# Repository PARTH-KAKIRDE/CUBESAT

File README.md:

# EPS — Electrical Power System

Power management module for the 2U CubeSat.

## Overview
Handles solar power generation, battery charging, and regulated power distribution to all subsystems (OBC, COMMS, ADCS, Payload).

## Contents
- `CubeSat_EPS/` — KiCad project (schematic + PCB + fabrication PDF)
  - `CubeSat_EPS.kicad_sch` — Schematic
  - `CubeSat_EPS.kicad_pcb` — PCB layout
  - `CubeSat_EPS.kicad_pro` — Project configuration
  - `CubeSat_EPS.pdf` — Schematic PDF export

## Tool
Designed in KiCad 7/8. Open `CubeSat_EPS.kicad_pro` to view the full project.

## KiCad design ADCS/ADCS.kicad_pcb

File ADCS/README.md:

# ADCS — Attitude Determination and Control System

STM32F446 board that reads the six sun sensors and drives the three magnetorquers (DRV8833 X/Y/Z).

## Contents
- `ADCS.kicad_sch` — Schematic
- `ADCS.kicad_pcb` — PCB layout (84 × 84 mm, 2 layers)
- `ADCS.kicad_pro` — Project configuration
- `fp-lib-table`, `Library.pretty/` — project footprint library (Tag-Connect TC2030 SWD)

## Protection and reliability changes
- Input protection on 5V and 3.3V: PTC fuses (F1 0.75 A, F2 0.5 A), reverse-polarity P-MOSFETs (Q1/Q2 AO3401A), TVS diodes (D1 SMBJ5.0A, D2 SMBJ3.3A)
- ESD diodes (ESD5B5) on the six sun-sensor inputs and both I2C buses (D3–D12)
- Decoupling: 47 µF bulk on 5V, 10 µF + 4.7 µF + 100 nF on 3.3V
- DRV8833 nFAULT lines pulled **up** to 3.3V (R12–R14, 10k); the pin is open-drain
- Current-sense outputs filtered (1k + 100 nF) before the ADC
- I2C pull-ups (4.7k), BOOT0 pull-down (10k)
- Single GND–GNDA tie (R20, 0R)
- Four 4 mm mounting holes, 75 mm spacing

## Checks
KiCad 10.0.6: DRC 0 violations, 0 unconnected pads. Two warnings: the F1/F2 footprints do not match the symbol's footprint filter (footprint is correct).

## Tool
Designed in KiCad 10. Open `ADCS.kicad_pro` to view the full project.

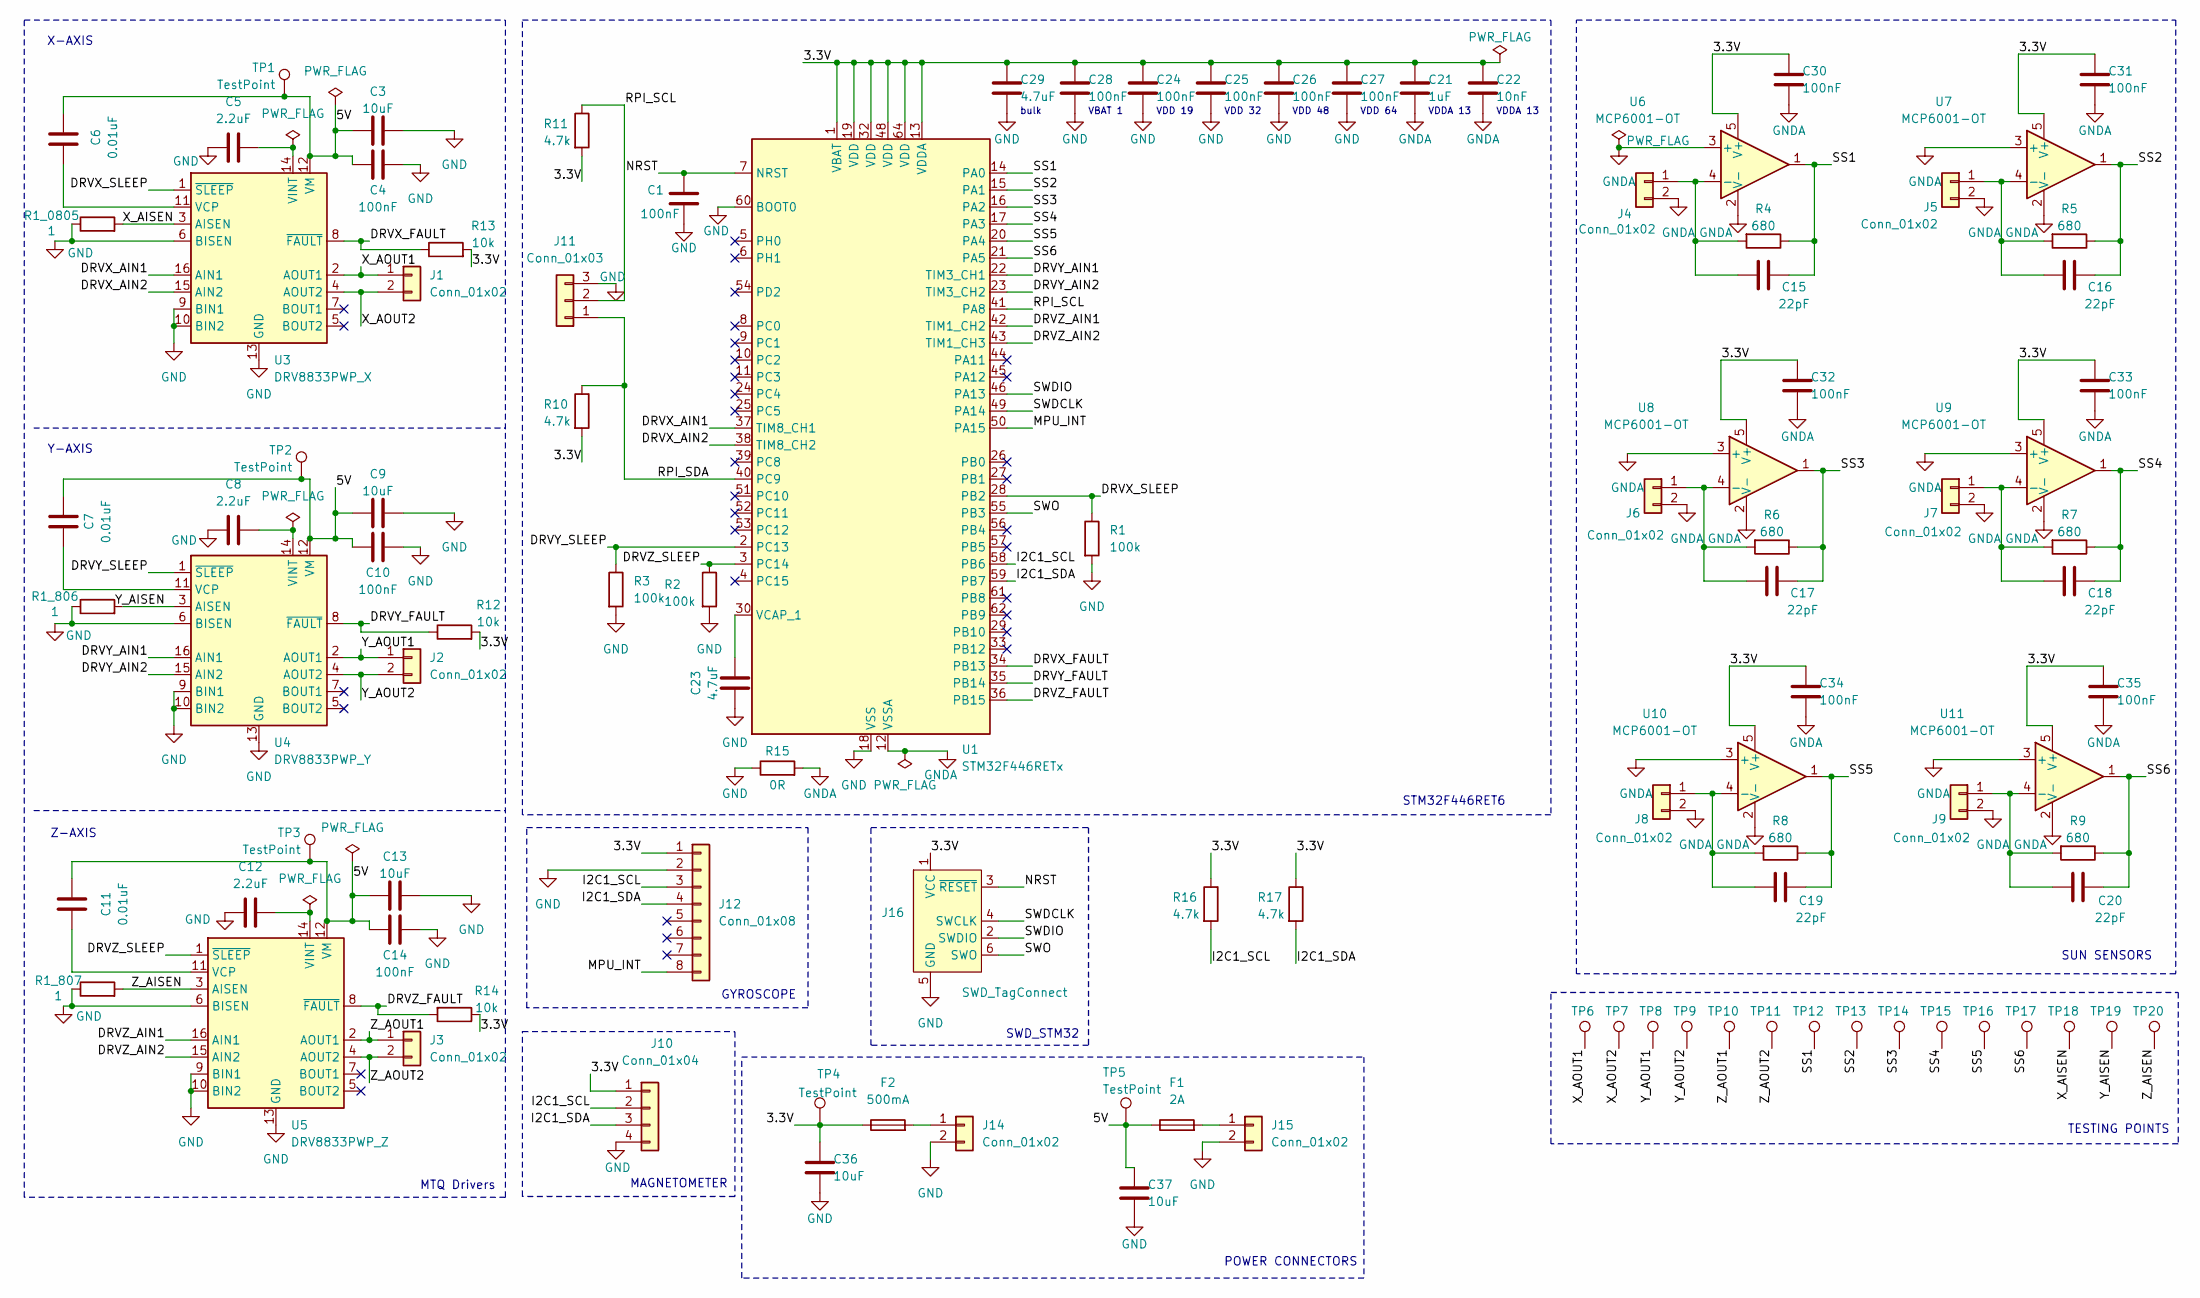
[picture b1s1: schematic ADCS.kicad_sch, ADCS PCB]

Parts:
C1, C4, C10, C14: 100nF; C_0805_2012Metric_Pad1.18x1.45mm_HandSolder
C3, C9, C13: 10uF; C_0805_2012Metric_Pad1.18x1.45mm_HandSolder
C5, C8, C12: 2.2uF; C_0805_2012Metric_Pad1.18x1.45mm_HandSolder
C6, C7, C11: 0.01uF; C_0805_2012Metric_Pad1.18x1.45mm_HandSolder
C15, C16, C17, C18, C19, C20: 22pF; C_0805_2012Metric_Pad1.18x1.45mm_HandSolder
C21: 1uF; C_0805_2012Metric_Pad1.18x1.45mm_HandSolder
C22: 10nF; C_0805_2012Metric_Pad1.18x1.45mm_HandSolder
C23, C29: 4.7uF; C_0805_2012Metric_Pad1.18x1.45mm_HandSolder
C24, C25, C26, C27, C28, C30, C31, C32, C33, C34, C35: 100nF; C_0603_1608Metric_Pad1.08x0.95mm_HandSolder
C36, C37: 10uF; C_1206_3216Metric_Pad1.33x1.80mm_HandSolder
F1: 2A; Fuse_1206_3216Metric_Pad1.42x1.75mm_HandSolder
F2: 500mA; Fuse_1206_3216Metric_Pad1.42x1.75mm_HandSolder
J1, J2, J3, J4, J5, J6, J7, J8, J9: Conn_01x02; JST_PH_B2B-PH-K_1x02_P2.00mm_Vertical
J10: Conn_01x04; JST_PH_B4B-PH-K_1x04_P2.00mm_Vertical
J11: Conn_01x03; JST_PH_B3B-PH-K_1x03_P2.00mm_Vertical
J12: Conn_01x08; JST_PH_B8B-PH-K_1x08_P2.00mm_Vertical
J14, J15: Conn_01x02; JST_XH_B2B-XH-AM_1x02_P2.50mm_Vertical
J16: SWD_TagConnect; Tag-Connect_TC2030-IDC-NL_2x03_P1.27mm_Vertical
R1, R2, R3: 100k; R_0805_2012Metric_Pad1.20x1.40mm_HandSolder
R1_0805, R1_806, R1_807: 1; R_0805_2012Metric_Pad1.20x1.40mm_HandSolder
R4, R5, R6, R7, R8, R9: 680; R_0805_2012Metric_Pad1.20x1.40mm_HandSolder
R10, R11, R16, R17: 4.7k; R_0805_2012Metric_Pad1.20x1.40mm_HandSolder
R12, R13, R14: 10k; R_0805_2012Metric_Pad1.20x1.40mm_HandSolder
R15: 0R; R_0805_2012Metric_Pad1.20x1.40mm_HandSolder
TP1, TP2, TP3, TP4, TP5, TP6, TP7, TP8, TP9, TP10, TP11, TP12, TP13, TP14, TP15, TP16, TP17, TP18, TP19, TP20: TestPoint; TestPoint_Pad_1.0x1.0mm
U1: STM32F446RETx; LQFP-64_10x10mm_P0.5mm
U3: DRV8833PWP_X; HTSSOP-16-1EP_4.4x5mm_P0.65mm_EP3.4x5mm_Mask2.46x2.31mm_The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
U4: DRV8833PWP_Y; HTSSOP-16-1EP_4.4x5mm_P0.65mm_EP3.4x5mm_Mask2.46x2.31mm_The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
U5: DRV8833PWP_Z; HTSSOP-16-1EP_4.4x5mm_P0.65mm_EP3.4x5mm_Mask2.46x2.31mm_The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
U6, U7, U8, U9, U10, U11: MCP6001-OT; SOT-23-5

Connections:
/3.3V: C21.1, C22.1, C24.1, C25.1, C26.1, C27.1, C28.1, C29.1, C30.1, C31.1, C32.1, C33.1, C34.1, C35.1, C36.1, F2.1, J10.1, J12.1, J16.1 (VCC), R10.2, R11.2, R12.2, R13.2, R14.1, R16.1, R17.1, TP4.1 (1_1), U1.1 (VBAT), U1.13 (VDDA), U1.19 (VDD), U1.32 (VDD), U1.48 (VDD), U1.64 (VDD), U6.5 (V+), U7.5 (V+), U8.5 (V+), U9.5 (V+), U10.5 (V+), U11.5 (V+)
/5V: C3.1, C4.1, C6.2, C7.2, C9.1, C10.1, C11.2, C13.1, C14.1, C37.1, F1.1, TP1.1 (1_1), TP2.1 (1_1), TP3.1 (1_1), TP5.1 (1_1), U3.12 (VM), U4.12 (VM), U5.12 (VM)
/DRVX_AIN1: U1.37 (TIM8_CH1), U3.16 (AIN1)
/DRVX_AIN2: U1.38 (TIM8_CH2), U3.15 (AIN2)
/DRVX_FAULT: R13.1, U1.34 (PB13), U3.8 (~FAULT)
/DRVX_SLEEP: R1.1, U1.28 (PB2), U3.1 (~SLEEP)
/DRVY_AIN1: U1.22 (TIM3_CH1), U4.16 (AIN1)
/DRVY_AIN2: U1.23 (TIM3_CH2), U4.15 (AIN2)
/DRVY_FAULT: R12.1, U1.35 (PB14), U4.8 (~FAULT)
/DRVY_SLEEP: R3.1, U1.2 (PC13), U4.1 (~SLEEP)
/DRVZ_AIN1: U1.42 (TIM1_CH2), U5.16 (AIN1)
/DRVZ_AIN2: U1.43 (TIM1_CH3), U5.15 (AIN2)
/DRVZ_FAULT: R14.2, U1.36 (PB15), U5.8 (~FAULT)
/DRVZ_SLEEP: R2.1, U1.3 (PC14), U5.1 (~SLEEP)
/I2C1_SCL: J10.2, J12.3, R16.2, U1.58 (PB6)
/I2C1_SDA: J10.3, J12.4, R17.2, U1.59 (PB7)
/MPU_INT: J12.8, U1.50 (PA15)
/NRST: C1.1, J16.3 (~RESET), U1.7 (NRST)
/RPI_SCL: J11.2, R11.1, U1.41 (PA8)
/RPI_SDA: J11.1, R10.1, U1.40 (PC9)
/SS1: C15.1, R4.1, TP12.1 (1_1), U1.14 (PA0), U6.1
/SS2: C16.1, R5.1, TP13.1 (1_1), U1.15 (PA1), U7.1
/SS3: C17.1, R6.1, TP14.1 (1_1), U1.16 (PA2), U8.1
/SS4: C18.1, R7.1, TP15.1 (1_1), U1.17 (PA3), U9.1
/SS5: C19.1, R8.1, TP16.1 (1_1), U1.20 (PA4), U10.1
/SS6: C20.1, R9.1, TP17.1 (1_1), U1.21 (PA5), U11.1
/SWDCLK: J16.4 (SWCLK), U1.49 (PA14)
/SWDIO: J16.2 (SWDIO), U1.46 (PA13)
/SWO: J16.6 (SWO), U1.55 (PB3)
/X_AISEN: R1_0805.2, TP18.1 (1_1), U3.3 (AISEN)
/X_AOUT1: J1.1, TP6.1 (1_1), U3.2 (AOUT1)
/X_AOUT2: J1.2, TP7.1 (1_1), U3.4 (AOUT2)
/Y_AISEN: R1_806.2, TP19.1 (1_1), U4.3 (AISEN)
/Y_AOUT1: J2.1, TP8.1 (1_1), U4.2 (AOUT1)
/Y_AOUT2: J2.2, TP9.1 (1_1), U4.4 (AOUT2)
/Z_AISEN: R1_807.2, TP20.1 (1_1), U5.3 (AISEN)
/Z_AOUT1: J3.1, TP10.1 (1_1), U5.2 (AOUT1)
/Z_AOUT2: J3.2, TP11.1 (1_1), U5.4 (AOUT2)
GND: C1.2, C3.2, C4.2, C5.1, C8.1, C9.2, C10.2, C12.1, C13.2, C14.2, C23.1, C24.2, C25.2, C26.2, C27.2, C28.2, C29.2, C36.2, C37.2, J10.4, J11.3, J12.2, J14.2, J15.2, J16.5 (GND), R1.2, R1_0805.1, R1_806.1, R1_807.1, R2.2, R3.2, R15.1, U1.18 (VSS), U1.31 (VSS), U1.47 (VSS), U1.60 (BOOT0), U1.63 (VSS), U3.6 (BISEN), U3.9 (BIN1), U3.10 (BIN2), U3.13 (GND), U3.17 (GND), U4.6 (BISEN), U4.9 (BIN1), U4.10 (BIN2), U4.13 (GND), U4.17 (GND), U5.6 (BISEN), U5.9 (BIN1), U5.10 (BIN2), U5.13 (GND), U5.17 (GND)
GNDA: C21.2, C22.2, C30.2, C31.2, C32.2, C33.2, C34.2, C35.2, J4.2, J5.2, J6.2, J7.2, J8.2, J9.2, R15.2, U1.12 (VSSA), U6.2 (V-), U6.3 (+), U7.2 (V-), U7.3 (+), U8.2 (V-), U8.3 (+), U9.2 (V-), U9.3 (+), U10.2 (V-), U10.3 (+), U11.2 (V-), U11.3 (+)
unnamed: C15.2, J4.1, R4.2, U6.4 (-)
unnamed: C16.2, J5.1, R5.2, U7.4 (-)
unnamed: C17.2, J6.1, R6.2, U8.4 (-)
unnamed: C18.2, J7.1, R7.2, U9.4 (-)
unnamed: C19.2, J8.1, R8.2, U10.4 (-)
unnamed: C20.2, J9.1, R9.2, U11.4 (-)
unnamed: F2.2, J14.1
unnamed: F1.2, J15.1
unnamed: C23.2, U1.30 (VCAP_1)
unnamed: C6.1, U3.11 (VCP)
unnamed: C5.2, U3.14 (VINT)
unnamed: C7.1, U4.11 (VCP)
unnamed: C8.2, U4.14 (VINT)
unnamed: C11.1, U5.11 (VCP)
unnamed: C12.2, U5.14 (VINT)

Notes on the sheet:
VDD 19
MTQ Drivers
VDDA 13
TESTING POINTS
bulk
GYROSCOPE
MAGNETOMETER
VBAT 1
Z-AXIS
VDD 64
SUN SENSORS
VDD 32
POWER CONNECTORS
Y-AXIS
VDD 48
STM32F446RET6
SWD_STM32
X-AXIS

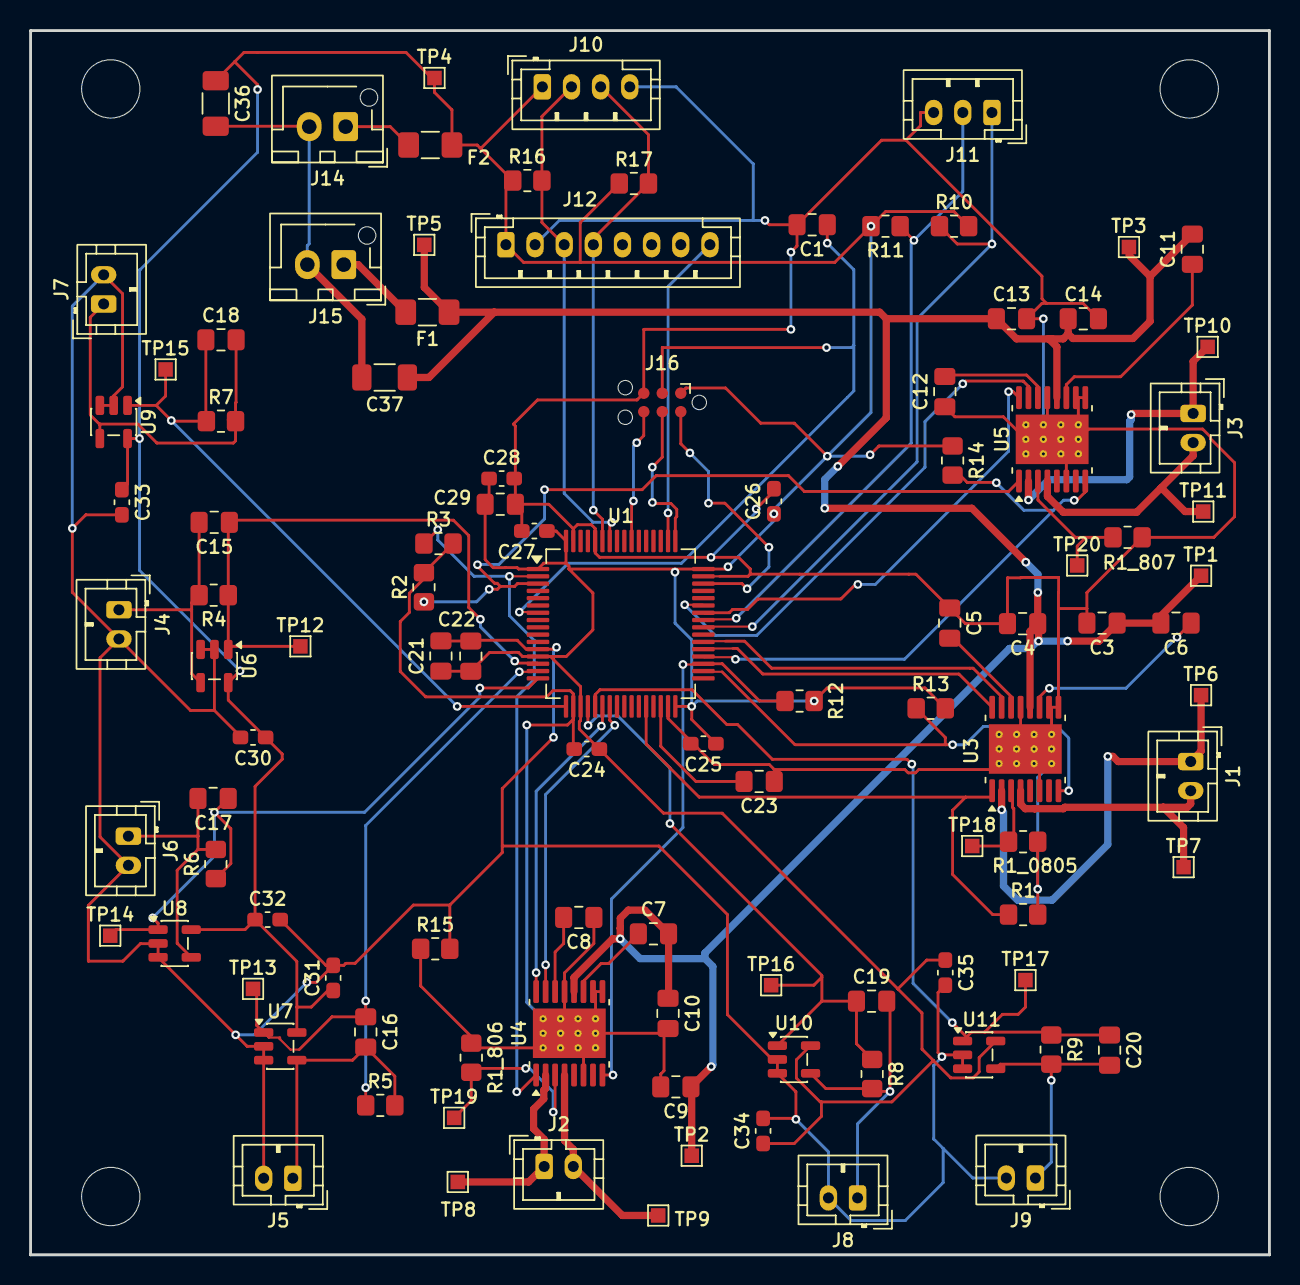
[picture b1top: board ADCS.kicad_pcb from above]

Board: 2 copper layers, 85.0 x 84.0 mm, 107 parts (0 on the bottom side), 55 nets.

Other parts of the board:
H1, H2, H3, H4: MountingHole_4mm

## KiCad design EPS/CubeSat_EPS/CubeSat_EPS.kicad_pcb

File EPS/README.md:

# EPS — Electrical Power System

Power management module for the 2U CubeSat.

## Overview
Handles solar power generation, battery charging, and regulated power distribution to all subsystems (OBC, COMMS, ADCS, Payload).

## Contents
- `CubeSat_EPS/` — KiCad project (schematic + PCB + fabrication PDF)
  - `CubeSat_EPS.kicad_sch` — Schematic
  - `CubeSat_EPS.kicad_pcb` — PCB layout
  - `CubeSat_EPS.kicad_pro` — Project configuration
  - `CubeSat_EPS.pdf` — Schematic PDF export

## Tool
Designed in KiCad 7/8. Open `CubeSat_EPS.kicad_pro` to view the full project.

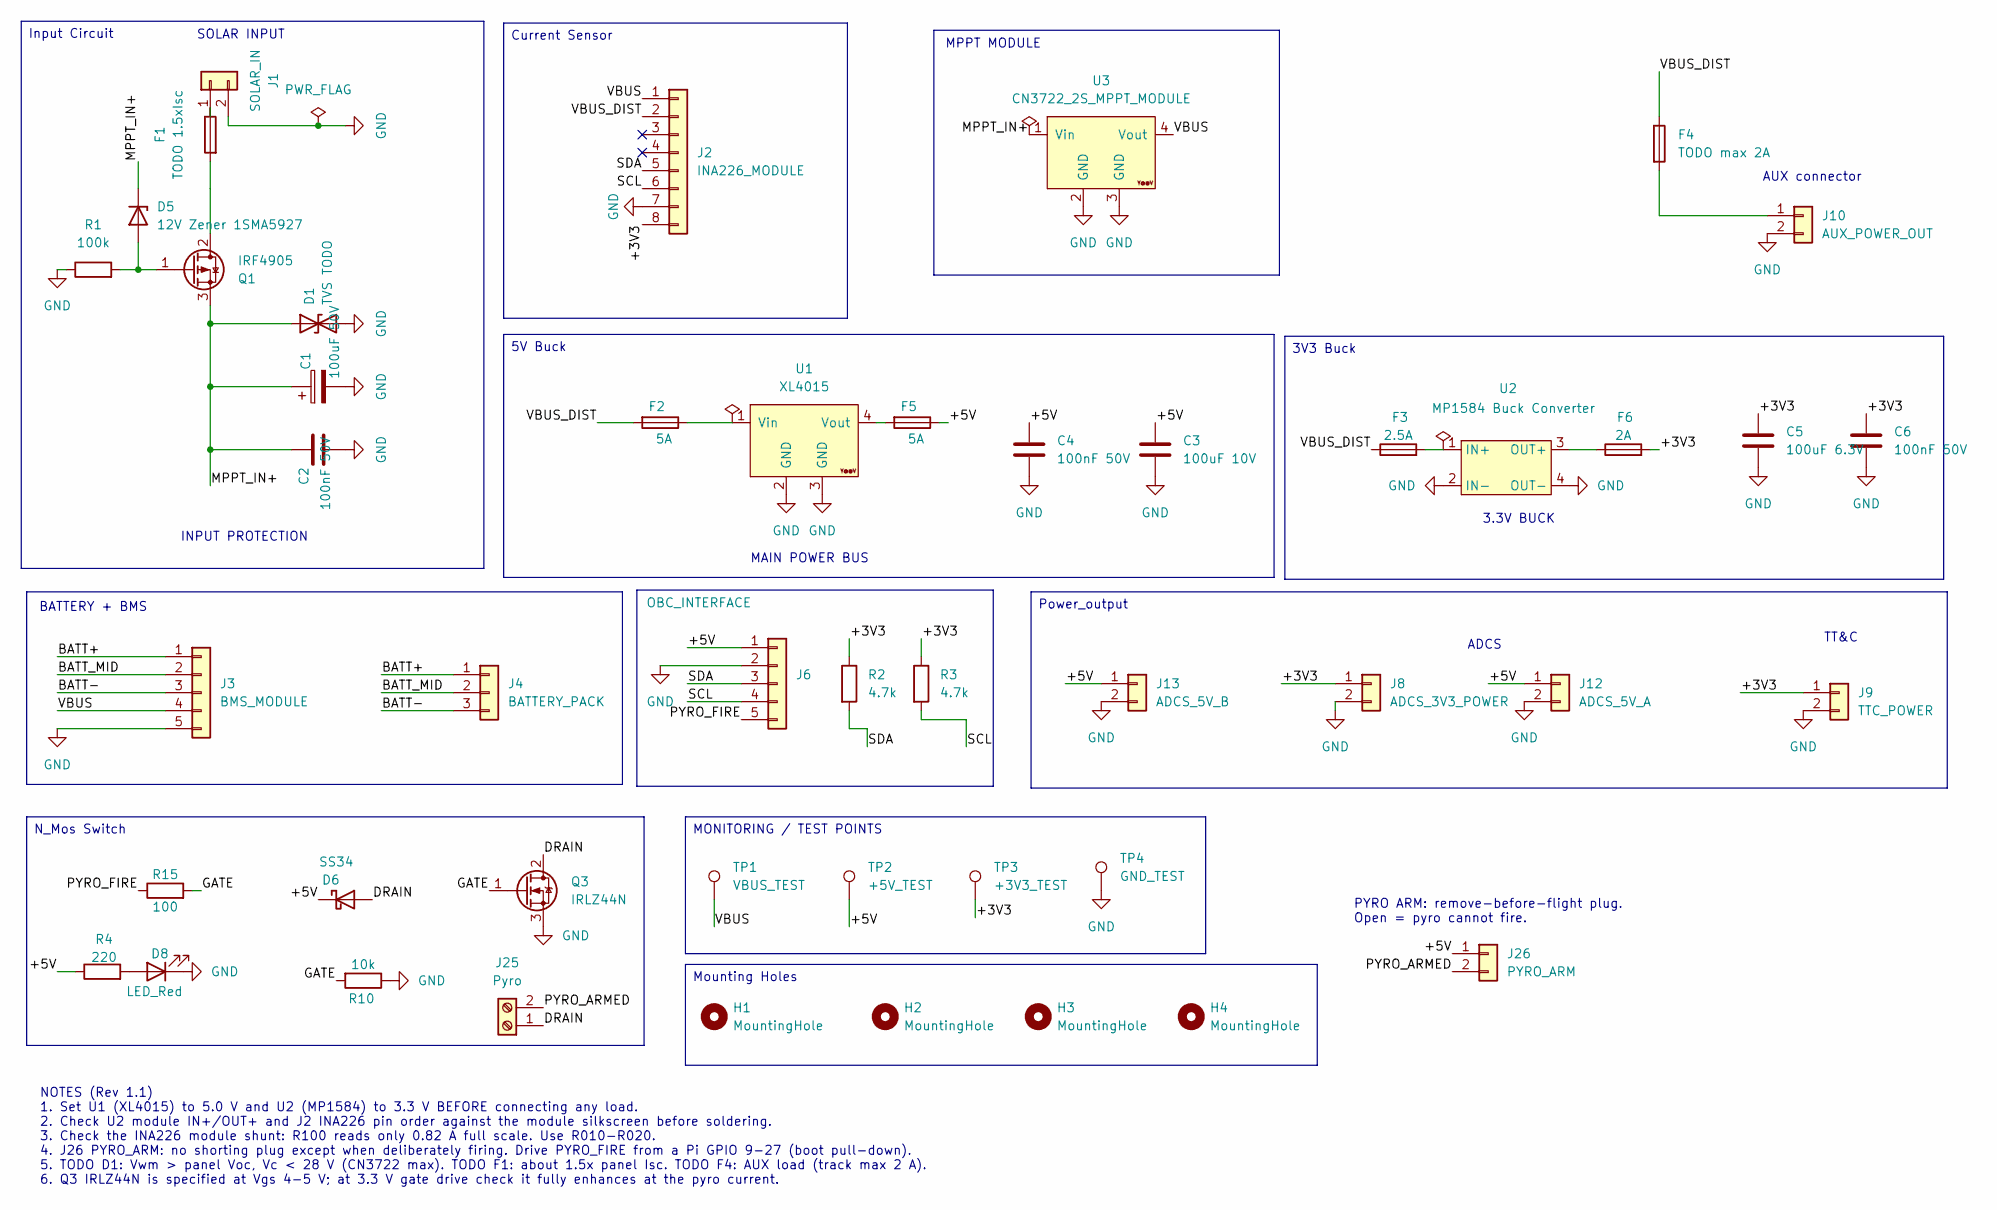
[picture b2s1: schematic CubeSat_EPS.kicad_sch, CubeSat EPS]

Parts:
C1: 100uF 50V; CP_Elec_6.3x7.7
C2, C4, C6: 100nF 50V; C_0805_2012Metric
C3: 100uF 10V; C_1206_3216Metric_Pad1.33x1.80mm_HandSolder
C5: 100uF 6.3V; C_0805_2012Metric_Pad1.18x1.45mm_HandSolder
D1: TVS TODO; D_SOD-123
D5: 12V Zener 1SMA5927; D_SMA
D6: SS34; D_SMA
D8: LED_Red; LED_0805_2012Metric_Pad1.15x1.40mm_HandSolder
F1: TODO 1.5xIsc; Fuse_1206_3216Metric
F2, F5: 5A; Fuse_1206_3216Metric
F3: 2.5A; Fuse_1206_3216Metric
F4: TODO max 2A; Fuse_1206_3216Metric
F6: 2A; Fuse_1206_3216Metric
H1, H2, H3, H4: MountingHole; MountingHole_4.3mm_M4
J1: SOLAR_IN; JST_VH_B2P-VH_1x02_P3.96mm_Vertical
J2: INA226_MODULE; INA226 Current Sensor
J3: BMS_MODULE; JST_VH_B5P-VH-B_1x05_P3.96mm_Vertical
J4: BATTERY_PACK; JST_VH_B3P-VH-B_1x03_P3.96mm_Vertical
J6: OBC_INTERFACE; JST_VH_B5P-VH_1x05_P3.96mm_Vertical
J8: ADCS_3V3_POWER; JST_VH_B2P-VH_1x02_P3.96mm_Vertical
J9: TTC_POWER; JST_VH_B2P-VH_1x02_P3.96mm_Vertical
J10: AUX_POWER_OUT; JST_VH_B2P-VH_1x02_P3.96mm_Vertical
J12: ADCS_5V_A; JST_VH_B2P-VH-B_1x02_P3.96mm_Vertical
J13: ADCS_5V_B; JST_VH_B2P-VH-B_1x02_P3.96mm_Vertical
J25: Pyro; TerminalBlock_TE_282834-2_1x02_P2.54mm_Horizontal
J26: PYRO_ARM; JST_VH_B2P-VH_1x02_P3.96mm_Vertical
Q1: IRF4905; TO-220-3_Vertical
Q3: IRLZ44N; TO-220-3_Vertical
R1: 100k; R_0805_2012Metric
R2, R3: 4.7k; R_0805_2012Metric
R4: 220; R_0805_2012Metric_Pad1.20x1.40mm_HandSolder
R10: 10k; R_0805_2012Metric_Pad1.20x1.40mm_HandSolder
R15: 100; R_0805_2012Metric_Pad1.20x1.40mm_HandSolder
TP1: VBUS_TEST; TestPoint_Pad_D1.5mm
TP2: +5V_TEST; TestPoint_Plated_Hole_D2.0mm
TP3: +3V3_TEST; TestPoint_Plated_Hole_D2.0mm
TP4: GND_TEST; TestPoint_Plated_Hole_D2.0mm
U1: XL4015; XL4015 Buck
U2: MP1584 Buck Converter; MP1584 module 20mm_15mm
U3: CN3722_2S_MPPT_MODULE; MPPT Solar

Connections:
/+3V3: C5.1, C6.1, F6.2, J2.8, J8.1, J9.1, R2.1, R3.1, TP3.1 (1_1)
/+5V: C3.1, C4.1, D6.1 (K), F5.1, J6.1, J12.1, J13.1, J26.1, R4.1, TP2.1 (1_1)
/BATT+: J3.1, J4.1
/BATT-: J3.3, J4.3
/BATT_MID: J3.2, J4.2
/DRAIN: D6.2 (A), J25.1, Q3.2 (D)
/GATE: Q3.1 (G), R10.2, R15.2
/MPPT_IN+: C1.1, C2.1, D1.1 (A1), D5.1 (K), Q1.3 (S), U3.1 (Vin)
/PYRO_ARMED: J25.2, J26.2
/PYRO_FIRE: J6.5, R15.1
/SCL: J2.6, J6.4, R3.2
/SDA: J2.5, J6.3, R2.2
/VBUS: J2.1, J3.4, TP1.1 (1_1), U3.4 (Vout)
/VBUS_DIST: F2.2, F3.1, F4.1, J2.2
GND: C1.2, C2.2, C3.2, C4.2, C5.2, C6.2, D1.2 (A2), D8.1 (K), J1.2, J2.7, J3.5, J6.2, J8.2, J9.2, J10.2, J12.2, J13.2, Q3.3 (S), R1.1, R10.1, TP4.1 (1_1), U1.2 (GND), U1.3 (GND), U2.2 (IN-), U2.4 (OUT-), U3.2 (GND), U3.3 (GND)
unnamed: D5.2 (A), Q1.1 (G), R1.2
unnamed: D8.2 (A), R4.2
unnamed: F1.1, J1.1
unnamed: F4.2, J10.1
unnamed: F1.2, Q1.2 (D)
unnamed: F2.1, U1.1 (Vin)
unnamed: F5.2, U1.4 (Vout)
unnamed: F3.2, U2.1 (IN+)
unnamed: F6.1, U2.3 (OUT+)

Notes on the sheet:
BATTERY + BMS
SOLAR INPUT
INPUT PROTECTION
MAIN POWER BUS
TT&C
AUX connector
ADCS
3.3V BUCK
MPPT MODULE
N_Mos Switch
MONITORING / TEST POINTS
3V3 Buck
Input Circuit
Power_output
5V Buck
Mounting Holes
Current Sensor
NOTES (Rev 1.1) 1. Set U1 (XL4015) to 5.0 V and U2 (MP1584) to 3.3 V BEFORE connecting any load. 2. Check U2 module IN+/OUT+ and J2 INA226 pin order against the module silkscreen before soldering. 3. Check the INA226 module shunt: R100 reads only 0.82 A full scale. Use R010-R020. 4. J26 PYRO_ARM: n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
PYRO ARM: remove-before-flight plug. Open = pyro cannot fire.

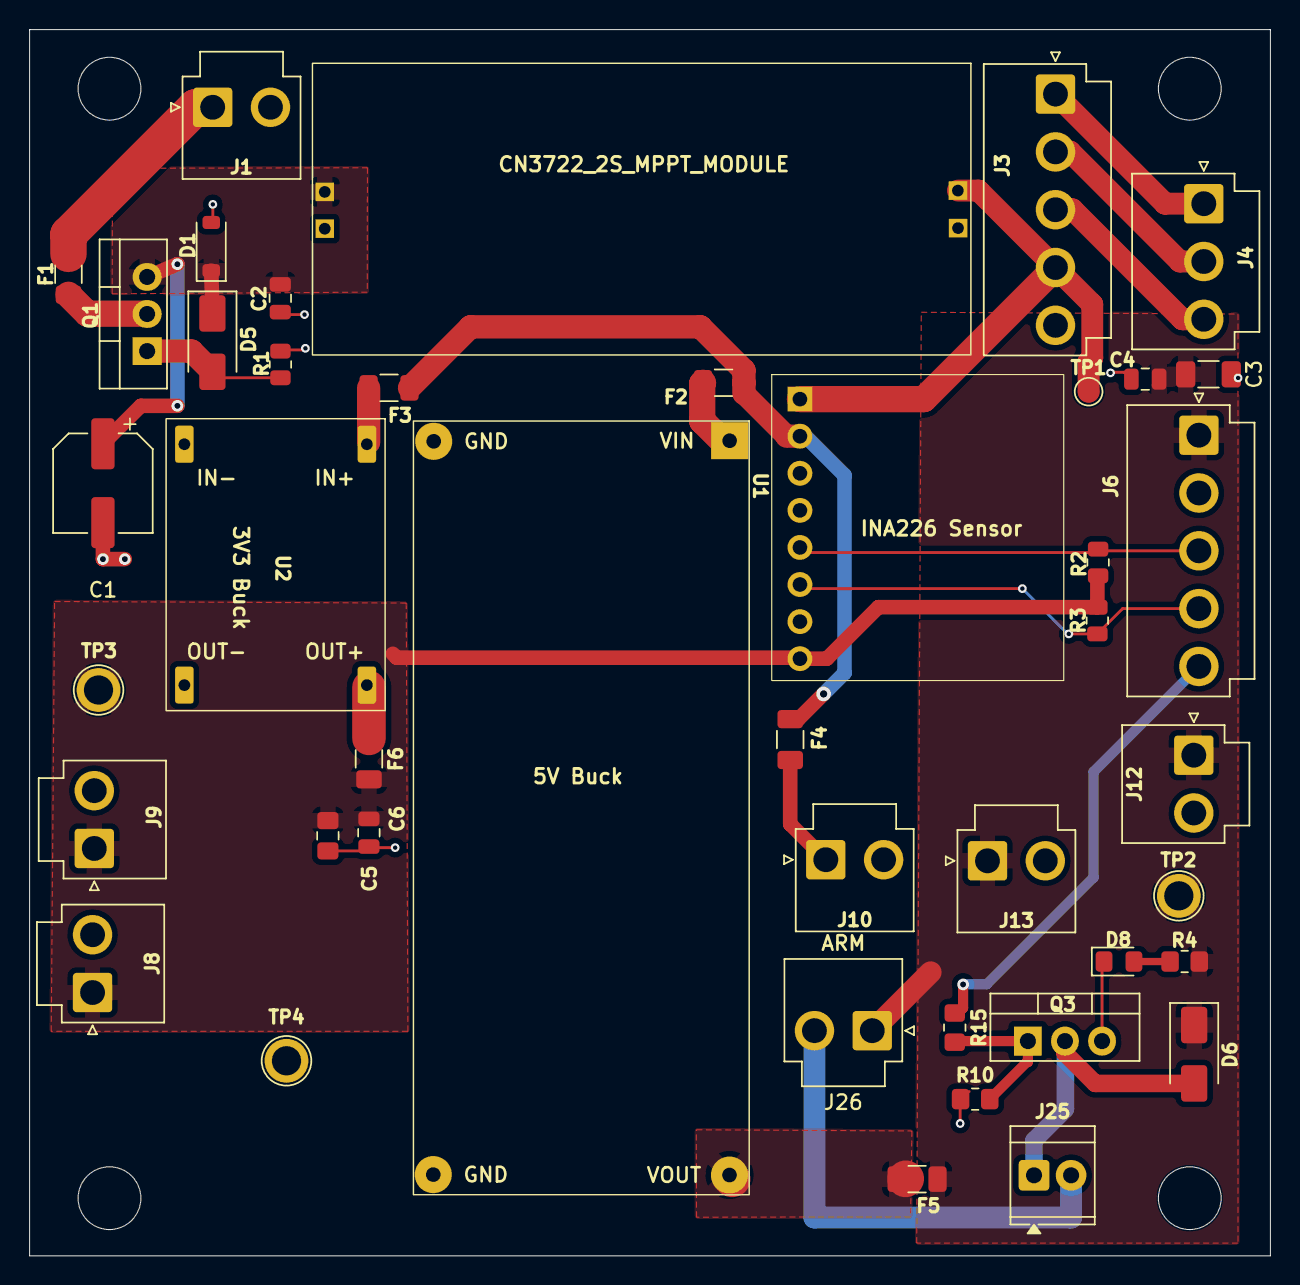
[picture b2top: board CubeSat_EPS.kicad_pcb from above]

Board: 2 copper layers, 85.0 x 84.0 mm, 47 parts (0 on the bottom side), 24 nets.
